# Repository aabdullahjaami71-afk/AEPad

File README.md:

# AEPad

The AEPad is a custom macropad designed for video editors. I made this macropad to make it easier and accelerate the time it takes 
for people to edit in video editing software. This macropad uses the RP2040 MCU, so be sure to put your MCU into bootloader mode to flash your own code onto the MCU

The case consists of a top and bottom layer, which can be assembled together with M3 inserts and screws.

# Here is the schematic, and PCB 

It comes with an OLED display for showing text and a rotary encoder for volume control!

# BOM
1 SEEEDUINO XIAO RP2040
9x Cherry MX switches
9x 1N4148 diodes
1x EC11 Rotary encoder
1x 0.91 inch OLED display
1x PCB 
4x M3 screws and inserts

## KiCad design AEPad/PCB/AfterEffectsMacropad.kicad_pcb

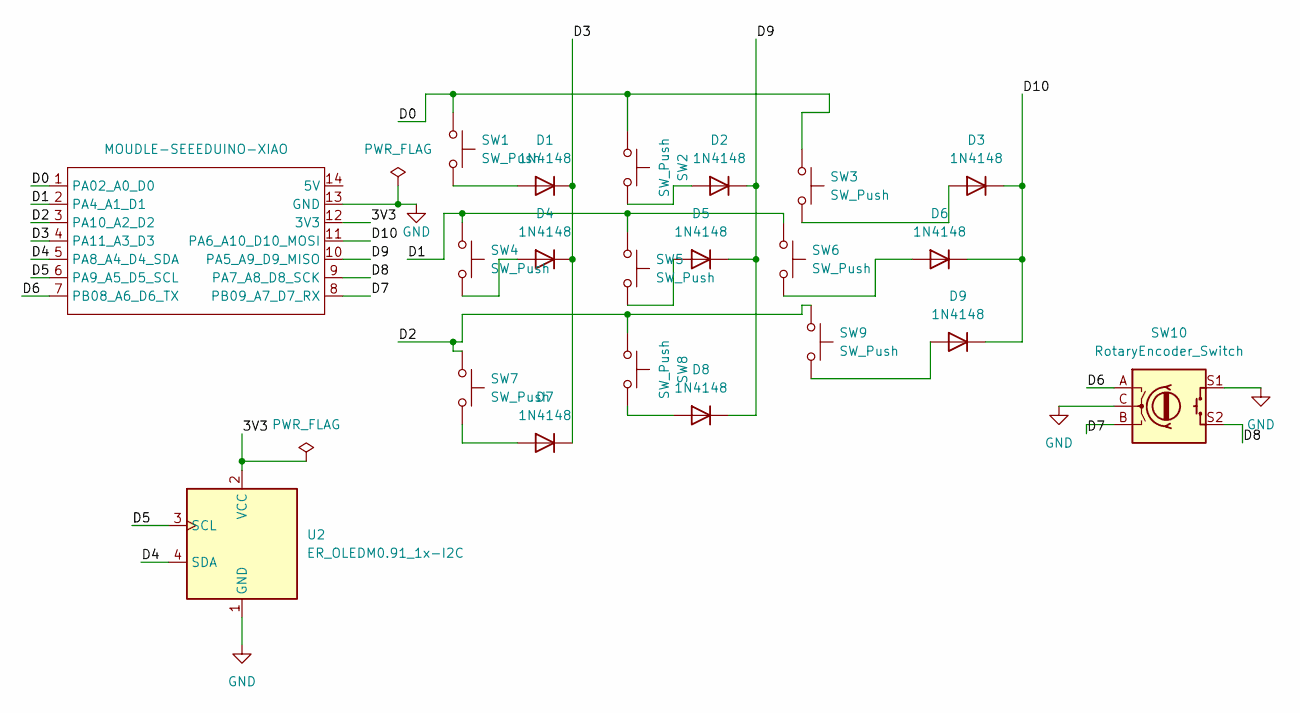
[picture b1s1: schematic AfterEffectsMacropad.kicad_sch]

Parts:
D1, D2, D3, D4, D5, D6, D7, D8, D9: 1N4148; D_DO-35_SOD27_P7.62mm_Horizontal
SW1, SW2, SW3, SW4, SW5, SW6, SW7, SW8, SW9: SW_Push; SW_Cherry_MX_1.00u_PCB
SW10: RotaryEncoder_Switch; RotaryEncoder_Alps_EC11E-Switch_Vertical_H20mm
U1: MOUDLE-SEEEDUINO-XIAO; XIAO-Generic-Hybrid-14P-2.54-21X17.8MM
U2: ER_OLEDM0.91_1x-I2C; SSD1306-0.91-OLED-4pin-128x32

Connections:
/3V3: U1.12 (3V3), U2.2 (VCC)
/D0: SW1.1, SW2.1, SW3.1, U1.1 (PA02_A0_D0)
/D1: SW4.1, SW5.1, SW6.1, U1.2 (PA4_A1_D1)
/D2: SW7.1, SW8.1, SW9.1, U1.3 (PA10_A2_D2)
/D3: D1.1 (K), D4.1 (K), D7.1 (K), U1.4 (PA11_A3_D3)
/D4: U1.5 (PA8_A4_D4_SDA), U2.4 (SDA)
/D5: U1.6 (PA9_A5_D5_SCL), U2.3 (SCL)
/D6: SW10.A, U1.7 (PB08_A6_D6_TX)
/D7: SW10.B, U1.8 (PB09_A7_D7_RX)
/D8: SW10.S2, U1.9 (PA7_A8_D8_SCK)
/D9: D2.1 (K), D5.1 (K), D8.1 (K), U1.10 (PA5_A9_D9_MISO)
/D10: D3.1 (K), D6.1 (K), D9.1 (K), U1.11 (PA6_A10_D10_MOSI)
GND: SW10.C, SW10.S1, U1.13 (GND), U2.1 (GND)
unnamed: D1.2 (A), SW1.2
unnamed: D2.2 (A), SW2.2
unnamed: D3.2 (A), SW3.2
unnamed: D4.2 (A), SW4.2
unnamed: D5.2 (A), SW5.2
unnamed: D6.2 (A), SW6.2
unnamed: D7.2 (A), SW7.2
unnamed: D8.2 (A), SW8.2
unnamed: D9.2 (A), SW9.2

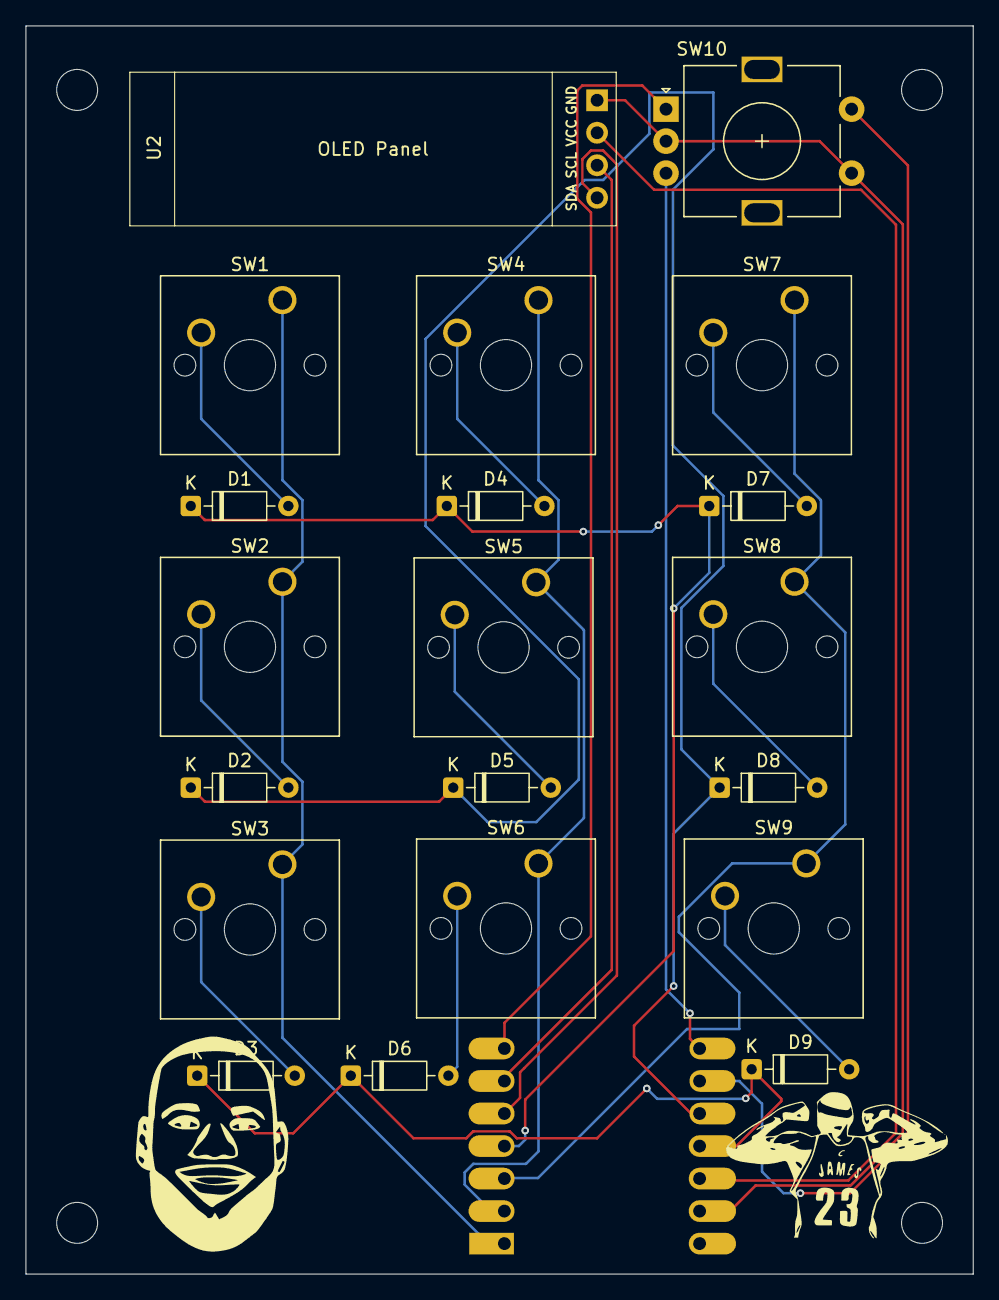
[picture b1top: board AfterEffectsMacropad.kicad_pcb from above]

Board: 2 copper layers, 74.0 x 97.5 mm, 21 parts (1 on the bottom side), 22 nets.
